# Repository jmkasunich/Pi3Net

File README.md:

# Pi3Net

Lightweight short-range networking for multiple Raspberry Pi Pico MCUs.

This project came about because I needed to connect 14 Raspberry Pi Pico boards together for a moving sculpture project.  As I designed my networking system I realised that it might be useful to others so I broke it out into its own project.

The name **Pi3Net** is short for **Pi Pico PIO Networking.**
* **Pi** is Raspberry Pi
* **Pico** is the Pico board, using the RP2040 MCU.  Unlike the regular Pi which runs Linux, the Pico is a lightweight MCU that usually runs firmware without an operating system.
* **PIO** is the RP2040's Programmable I/O unit, a dedicated co-processor that offloads bit-banging type I/O from the main processor and lets you develop custom interfaces.
* **Networking** is communication between a group of MCUs.

Although in some cases Pi3Net uses ethernet-style RJ45 connectors, it is NOT ethernet.  It is a very lightweight interface, implementing only a couple layers of the traditional networking model.  There are no IP addresses, no DHCP, no routers, sockets, etc.  It is just a way to quickly and efficiently send messages between MCUs.  The physical layer can be as simple as a single wire (plus ground), which works well if both MCUs are on the same board.  If the MCUs are further apart, on different boards, or in a noisy environment, you can add line drivers and recievers using RS-422 or RS-485 differential signals for better data integrity.  This project includes an open-source PC board design with line drivers and connectors to make it simple.

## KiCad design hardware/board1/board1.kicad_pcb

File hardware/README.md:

# Hardware
While the Pi3Net library doesn't need dedicated hardware, systems using physically long network segments or working in electricially noisy environments benefit from hardware line drivers and recievers that use differential signaling.  And pretty much any multi-board system needs terminals or connectors for the between-board wiring.

This repo contains hardware designs (KiCad 9 format) for boards that might be useful.

## Board 1
Board design 1 uses standard RJ54 type connectors (also known as 8p8c connectors).  These connectors are usually used for ethernet, and CAT5 or better cables with four twisted pairs are readily available in a variety of lengths at very low cost.
This board is intended to connect multiple Picos in a loop or straight-line configuration.  There are two connectors, one goes to the upstream neighbor and one goes downstream.
When fully populated, the board provides the following:
* two half-duplex links that connect all boards
* one full-duplex link connected to the upstream neighbor
* one full-duplex link connected to the downstream neighbor

Each link consumes two Pico pins.  You can choose how many drivers to install based on your needs.  If all you need is a single half-duplex global link, install one driver chip that uses two pins.

All pins that are not used by the communication links are passed through the board.  The intent is to use stacking headers, so that a Pico with this board attached can plug into a breadboard or any other board that would use a "naked" Pico.

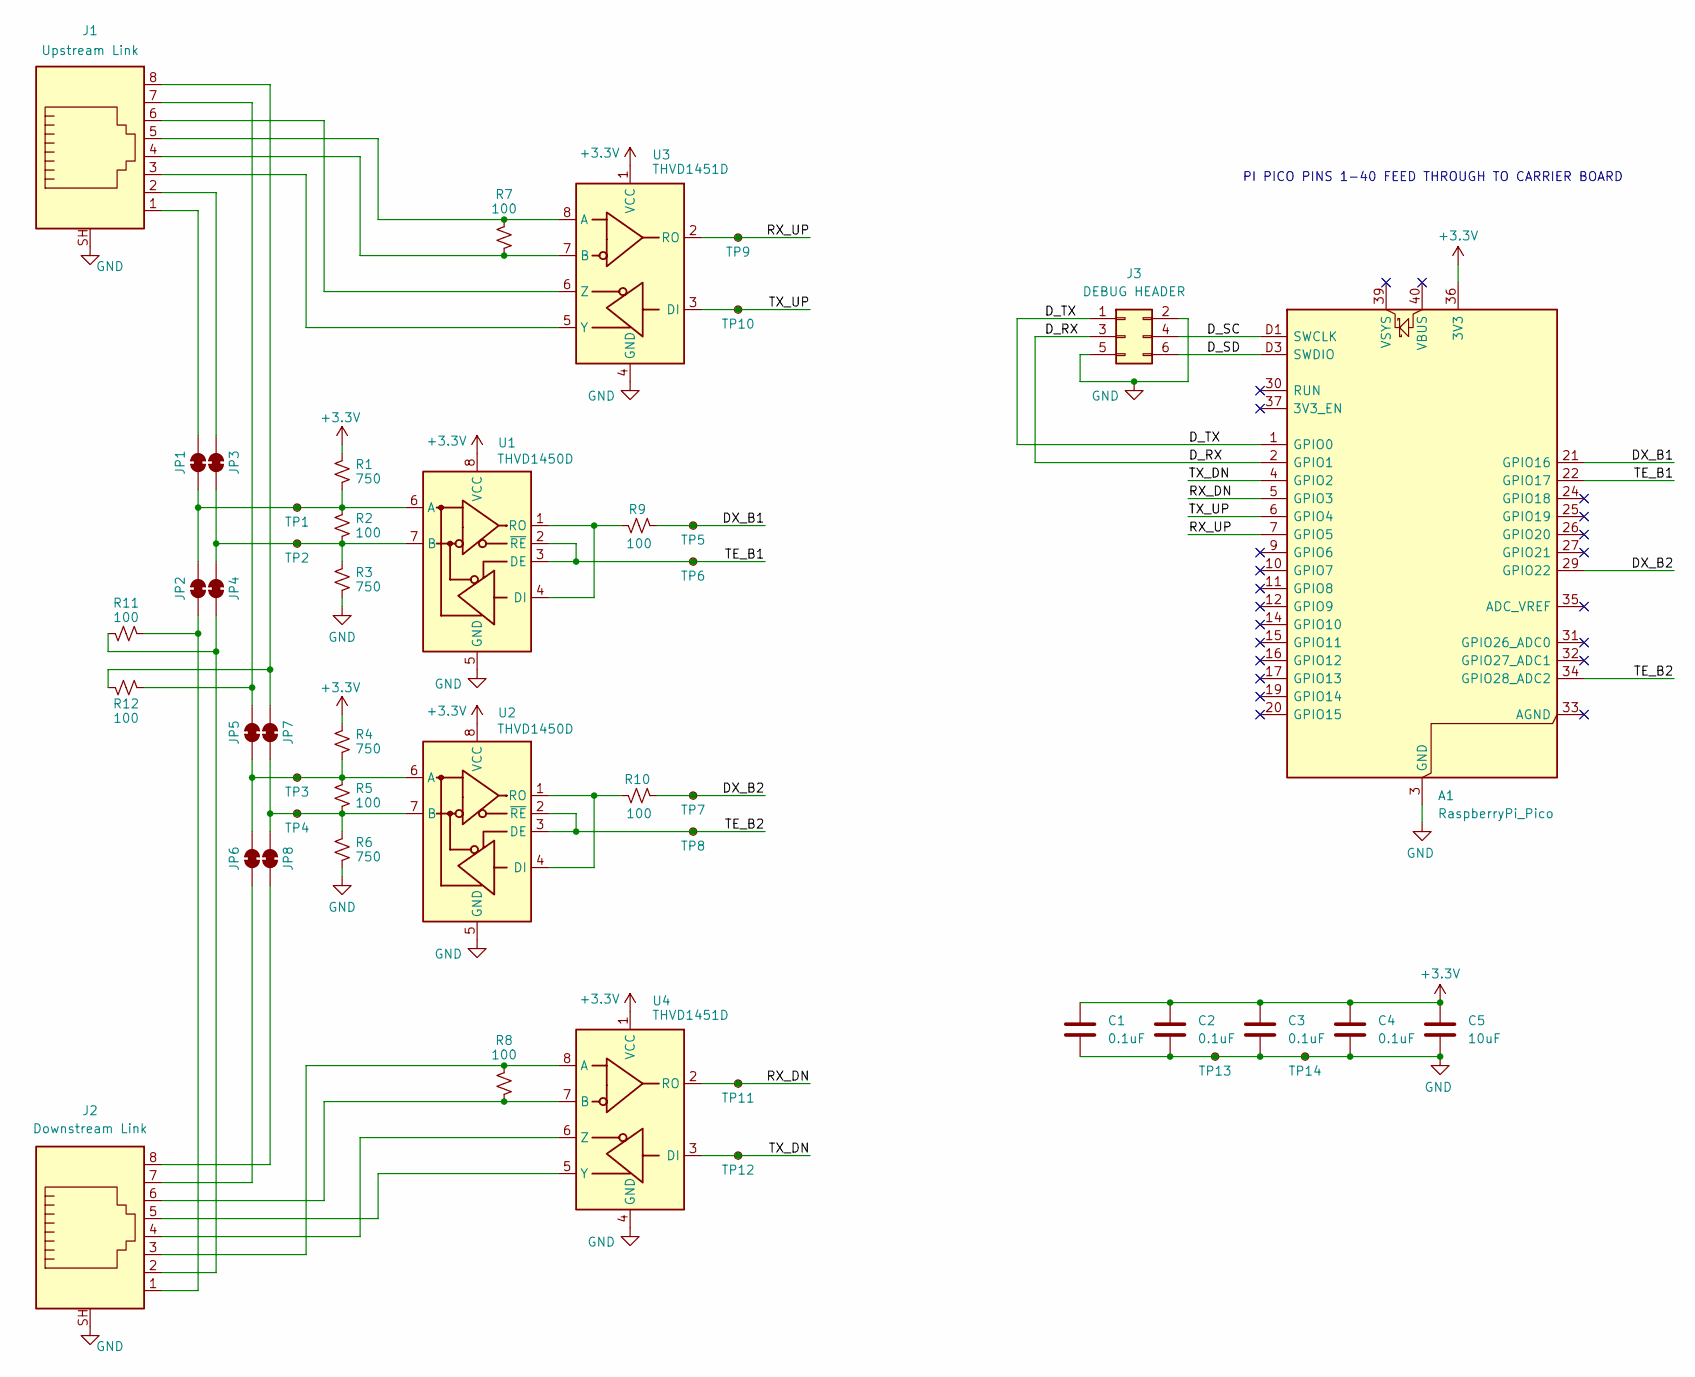
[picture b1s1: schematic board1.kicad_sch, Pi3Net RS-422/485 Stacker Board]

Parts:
A1: RaspberryPi_Pico; RaspberryPi_Pico_Debug_THT
C1, C2, C3, C4: 0.1uF; C_0805_2012Metric_Pad1.18x1.45mm_HandSolder
C5: 10uF; C_0805_2012Metric_Pad1.18x1.45mm_HandSolder
J1, J2: 8P8C_Shielded; RJ45_Amphenol_RJHSE5380
J3: DEBUG HEADER; IDC-Header_2x03_P2.54mm_Vertical
JP1, JP2, JP3, JP4, JP5, JP6, JP7, JP8: SolderJumper_2_Bridged; SolderJumper-2_P1.3mm_Bridged_Pad1.0x1.5mm
R1, R3, R4, R6: 750; R_0805_2012Metric_Pad1.20x1.40mm_HandSolder
R2, R5, R7, R8, R9, R10, R11, R12: 100; R_0805_2012Metric_Pad1.20x1.40mm_HandSolder
TP1, TP2, TP3, TP4, TP5, TP6, TP7, TP8, TP9, TP10, TP11, TP12, TP13, TP14: TestPoint_Small; TestPoint_THTPad_D2.0mm_Drill1.0mm
U1, U2: THVD1450D; SOIC-8_3.9x4.9mm_P1.27mm
U3, U4: THVD1451D; SOIC-8_3.9x4.9mm_P1.27mm

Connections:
+3.3V: A1.36 (3V3), C1.1, C2.1, C3.1, C4.1, C5.1, R1.1, R4.1, U1.8 (VCC), U2.8 (VCC), U3.1 (VCC), U4.1 (VCC)
/DX_B1: A1.21 (GPIO16), R9.2, TP5.1
/DX_B2: A1.29 (GPIO22), R10.2, TP7.1
/D_RX: A1.2 (GPIO1), J3.3
/D_SC: A1.D1 (SWCLK), J3.4
/D_SD: A1.D3 (SWDIO), J3.6
/D_TX: A1.1 (GPIO0), J3.1
/RX_DN: A1.5 (GPIO3), TP11.1, U4.2 (RO)
/RX_UP: A1.7 (GPIO5), TP9.1, U3.2 (RO)
/TE_B1: A1.22 (GPIO17), TP6.1, U1.2 (~RE), U1.3 (DE)
/TE_B2: A1.34 (GPIO28_ADC2), TP8.1, U2.2 (~RE), U2.3 (DE)
/TX_DN: A1.4 (GPIO2), TP12.1, U4.3 (DI)
/TX_UP: A1.6 (GPIO4), TP10.1, U3.3 (DI)
GND: A1.3 (GND), A1.8 (GND), A1.13 (GND), A1.18 (GND), A1.23 (GND), A1.28 (GND), A1.38 (GND), A1.D2 (GND), C1.2, C2.2, C3.2, C4.2, C5.2, J1.SH, J2.SH, J3.2, J3.5, R3.2, R6.2, TP13.1, TP14.1, U1.5 (GND), U2.5 (GND), U3.4 (GND), U4.4 (GND)
unnamed: J1.1, JP1.1 (A)
unnamed: JP1.2 (B), JP2.1 (A), R1.2, R2.1, TP1.1, U1.6 (A)
unnamed: J2.1, JP2.2 (B), R11.2
unnamed: J1.2, JP3.1 (A)
unnamed: JP3.2 (B), JP4.1 (A), R2.2, R3.1, TP2.1, U1.7 (B)
unnamed: J2.2, JP4.2 (B), R11.1
unnamed: J1.7, JP5.1 (A), R12.2
unnamed: JP5.2 (B), JP6.1 (A), R4.2, R5.1, TP3.1, U2.6 (A)
unnamed: J2.7, JP6.2 (B)
unnamed: J1.8, JP7.1 (A), R12.1
unnamed: JP7.2 (B), JP8.1 (A), R5.2, R6.1, TP4.1, U2.7 (B)
unnamed: J2.8, JP8.2 (B)
unnamed: R9.1, U1.1 (RO), U1.4 (DI)
unnamed: R10.1, U2.1 (RO), U2.4 (DI)
unnamed: J1.5, R7.1, U3.8 (A)
unnamed: J1.4, R7.2, U3.7 (B)
unnamed: J1.3, U3.5 (Y)
unnamed: J1.6, U3.6 (Z)
unnamed: J2.3, R8.1, U4.8 (A)
unnamed: J2.6, R8.2, U4.7 (B)
unnamed: J2.5, U4.5 (Y)
unnamed: J2.4, U4.6 (Z)

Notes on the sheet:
PI PICO PINS 1-40 FEED THROUGH TO CARRIER BOARD

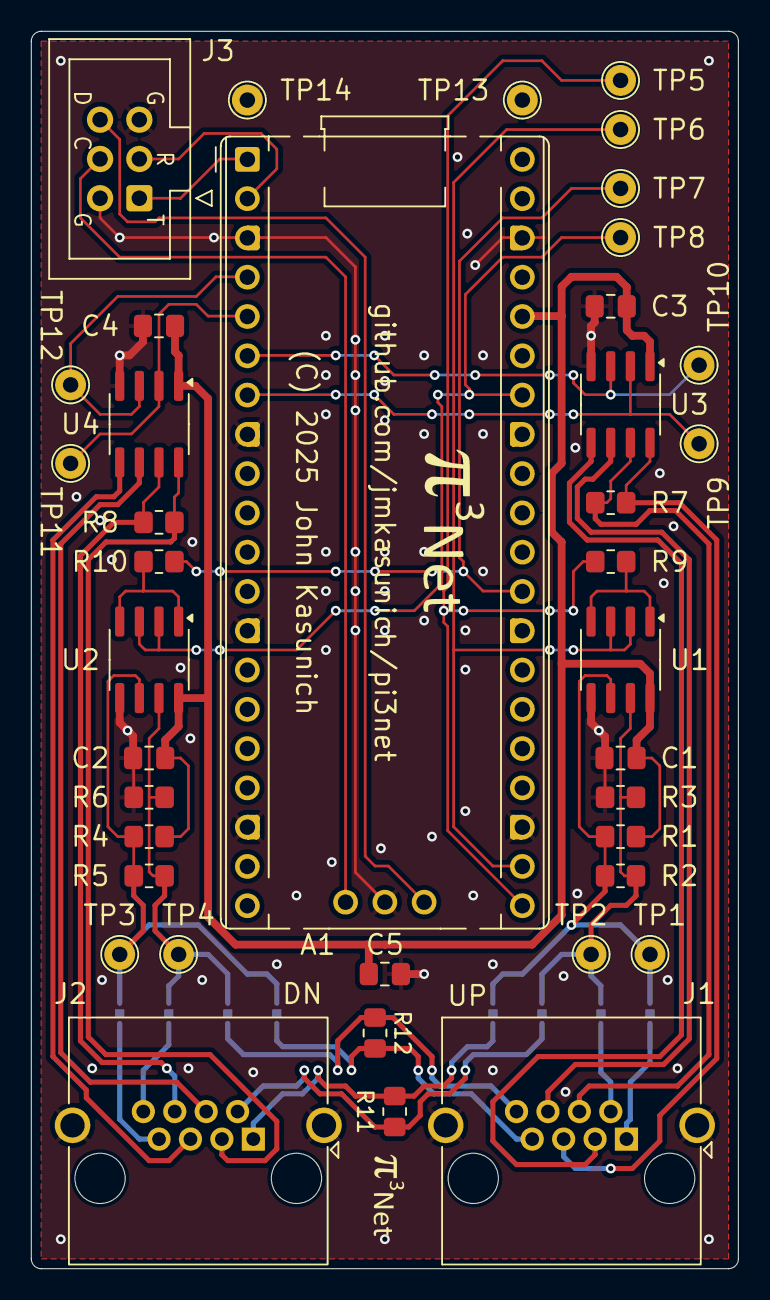
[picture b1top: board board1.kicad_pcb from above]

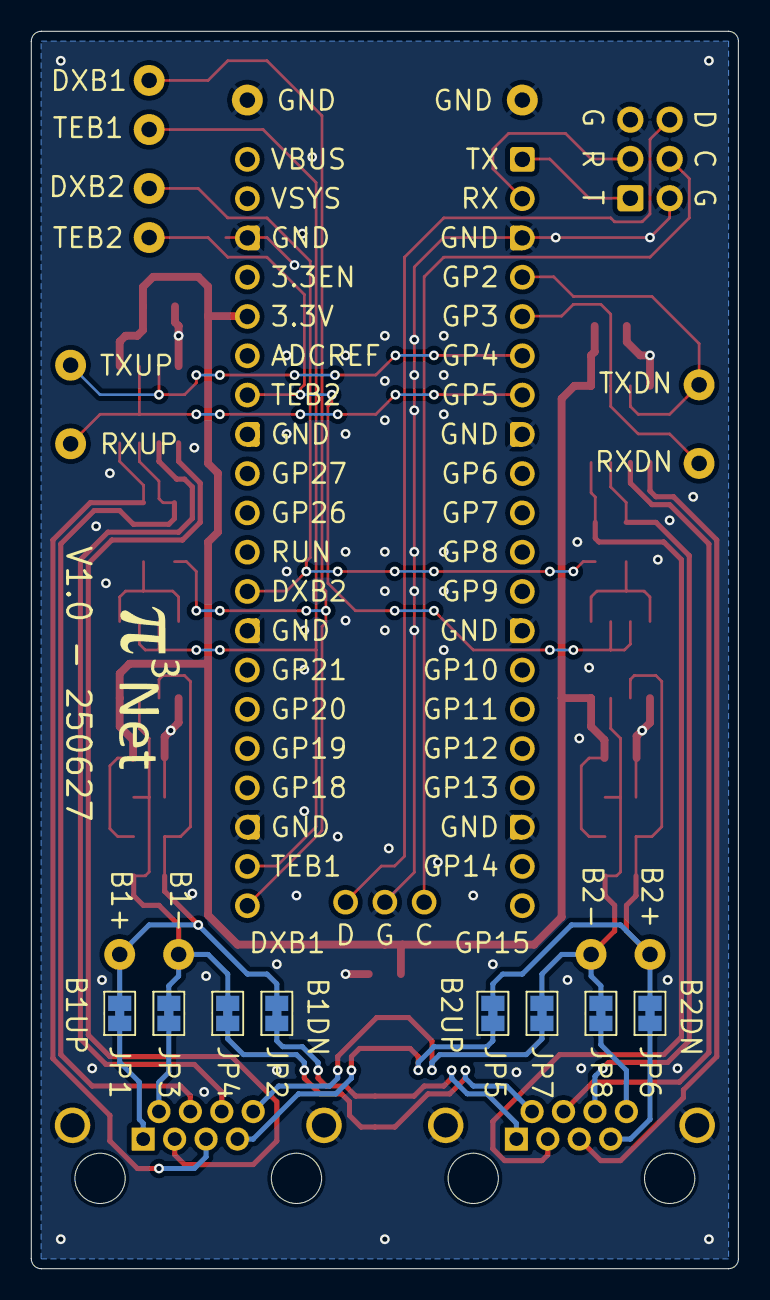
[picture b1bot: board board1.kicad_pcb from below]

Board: 2 copper layers, 45.7 x 80.0 mm, 47 parts (8 on the bottom side), 36 nets.

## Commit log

2025-06-30 initial commit of first board layout
2025-06-30 hardware readme
2025-06-30 add firmware directory
2025-06-30 inital commit of firmware; empty files and CMake stuff
2025-06-30 add hardware definitions
2025-07-03 initial work on PIO code
2025-07-05 work in progress; capturing a working snapshot
2025-07-06 got it working with interrupts and DMA, 10Mbaud
2025-07-13 testing and a bit of restructuring
2025-07-13 add CRC generation and checking; increase bit rate to 10 Mbps
2025-07-13 update kicad project file
2025-07-15 work in progress
2025-07-20 finished refactor; compiles and seems to work, much testing needed
2025-07-20 rearranged sideset for better scope observation; added test code
2025-07-21 got queued commands working, needs more testing
2025-07-24 removed busywait functions; they belong in their own library
2025-07-25 add simple blocking receive (with timout) and transmit functions
2025-07-25 fix some bugs in the CRC implementation
2025-07-25 cleanup, disable test code
2025-07-26 adjust rx DMA length to allow for CRC
2025-07-27 fix CRC bug
2025-07-27 add simple receive function without timeout, rename the original one
2025-08-17 fix static assert and include files

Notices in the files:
hardware/board1/board1.kicad_pcb:
(C) 2025 John Kasunich
